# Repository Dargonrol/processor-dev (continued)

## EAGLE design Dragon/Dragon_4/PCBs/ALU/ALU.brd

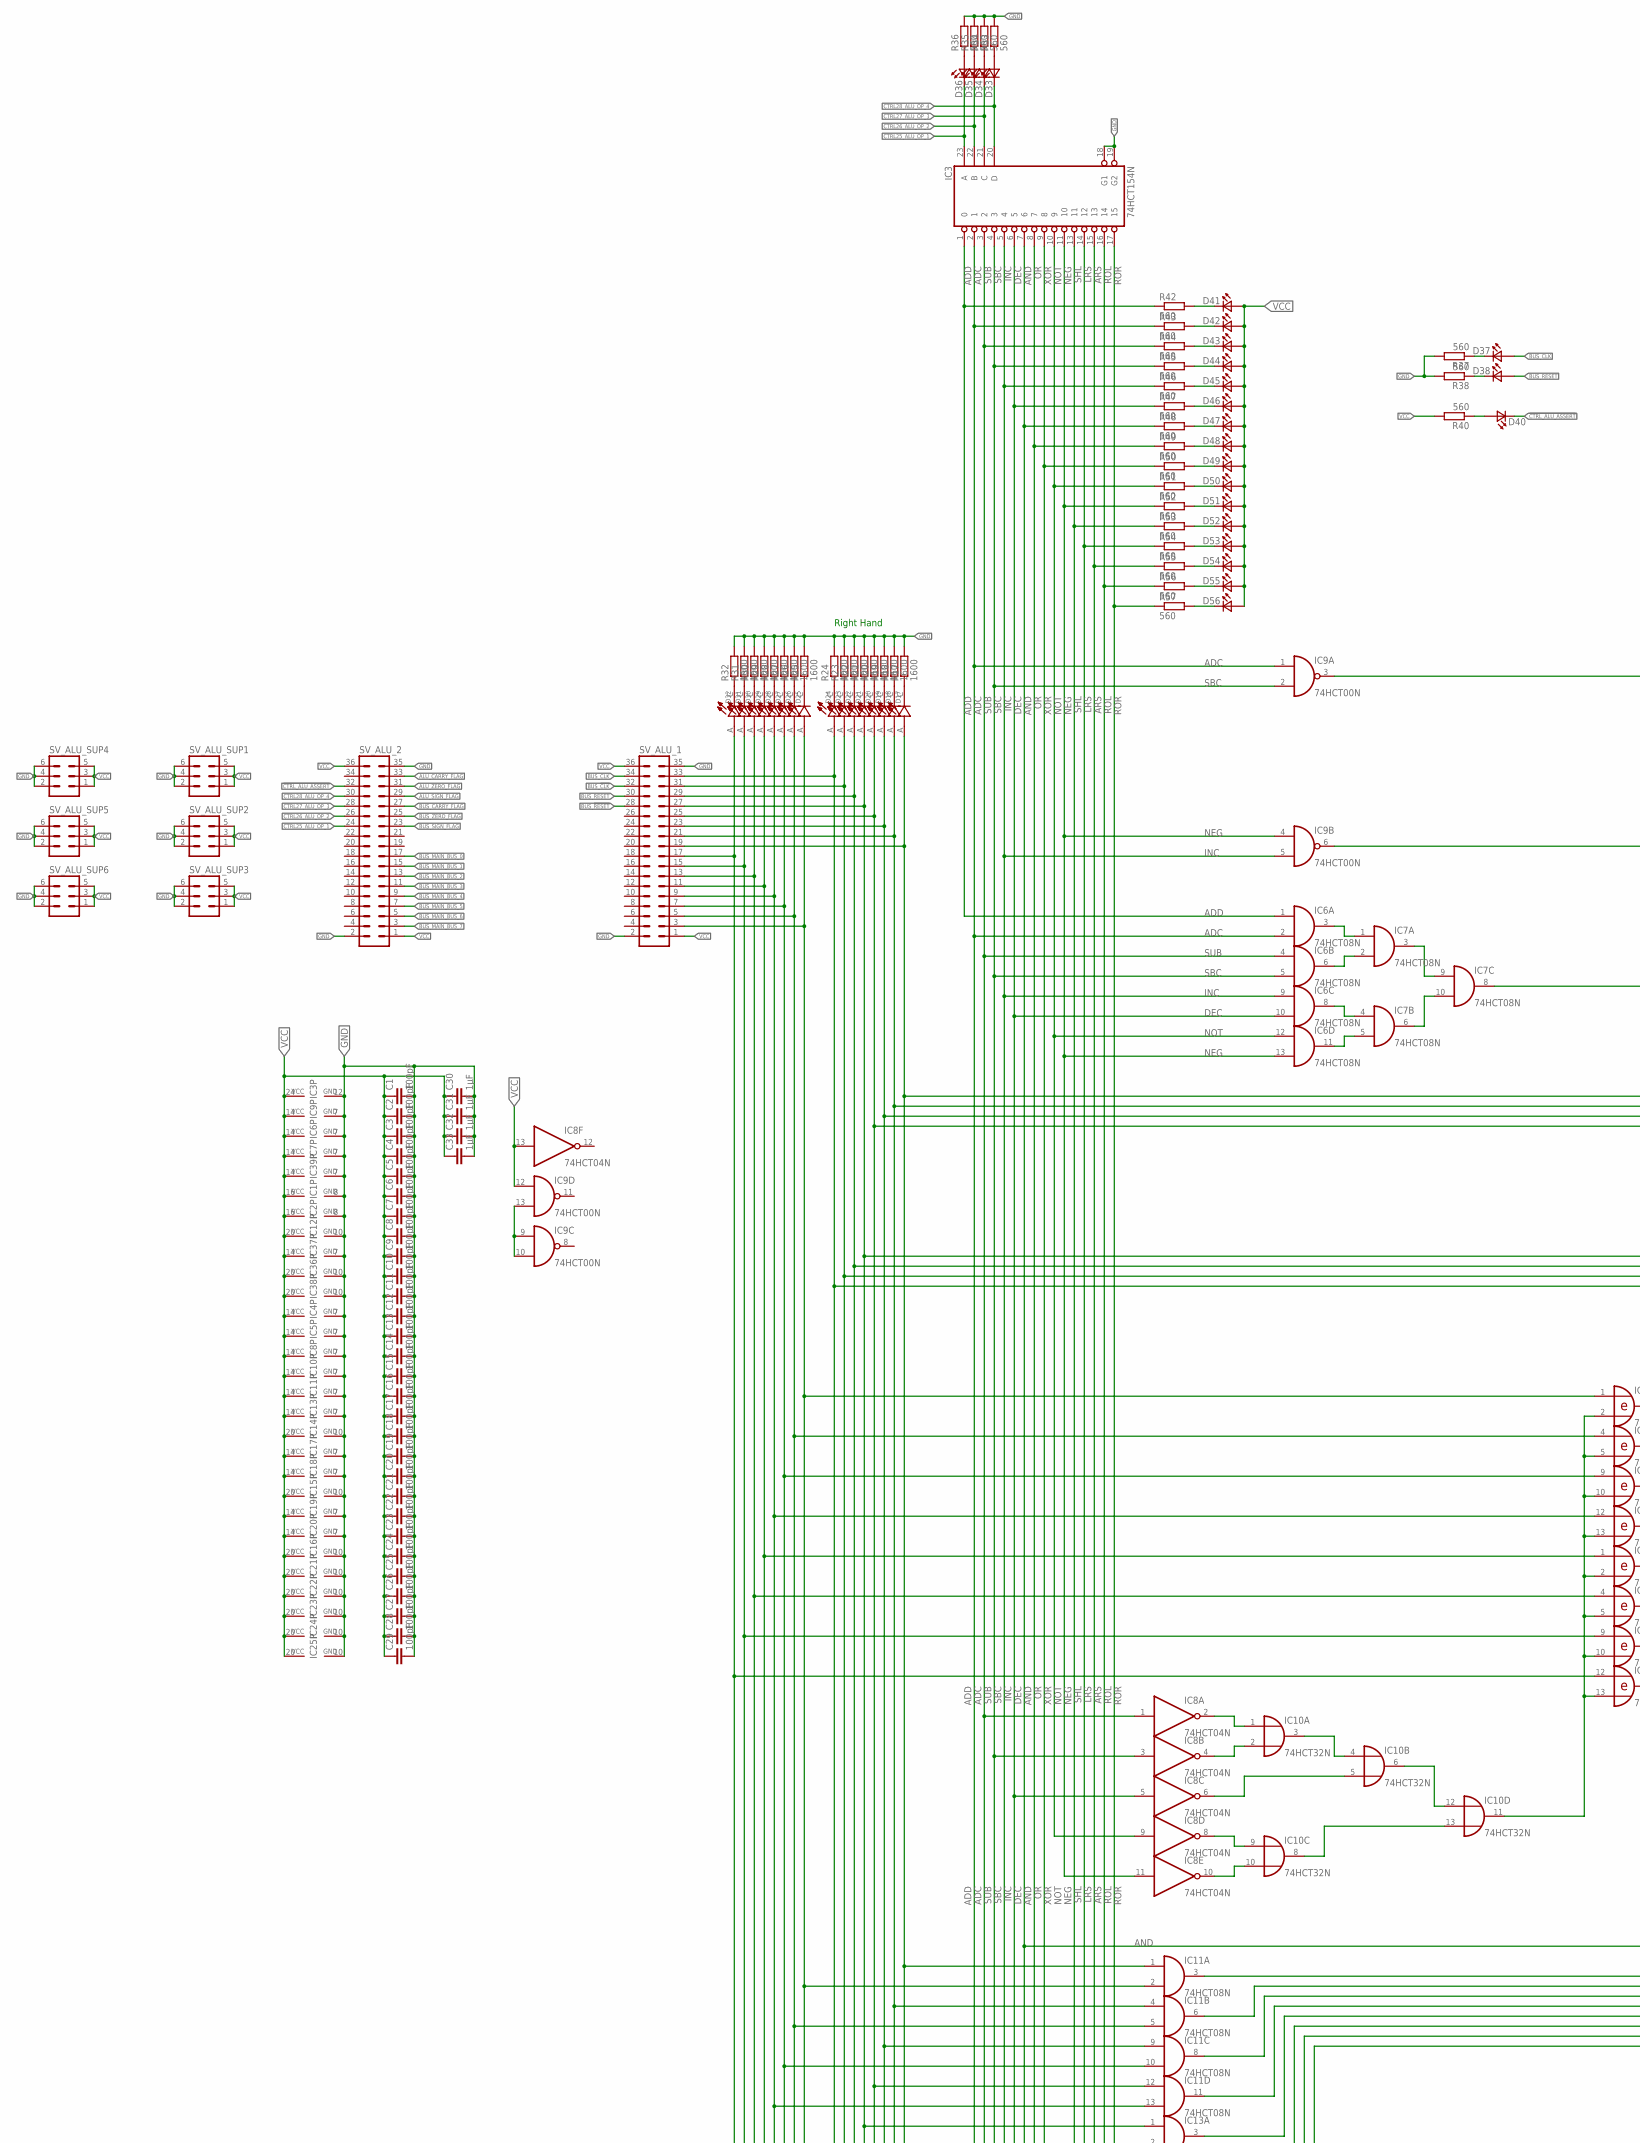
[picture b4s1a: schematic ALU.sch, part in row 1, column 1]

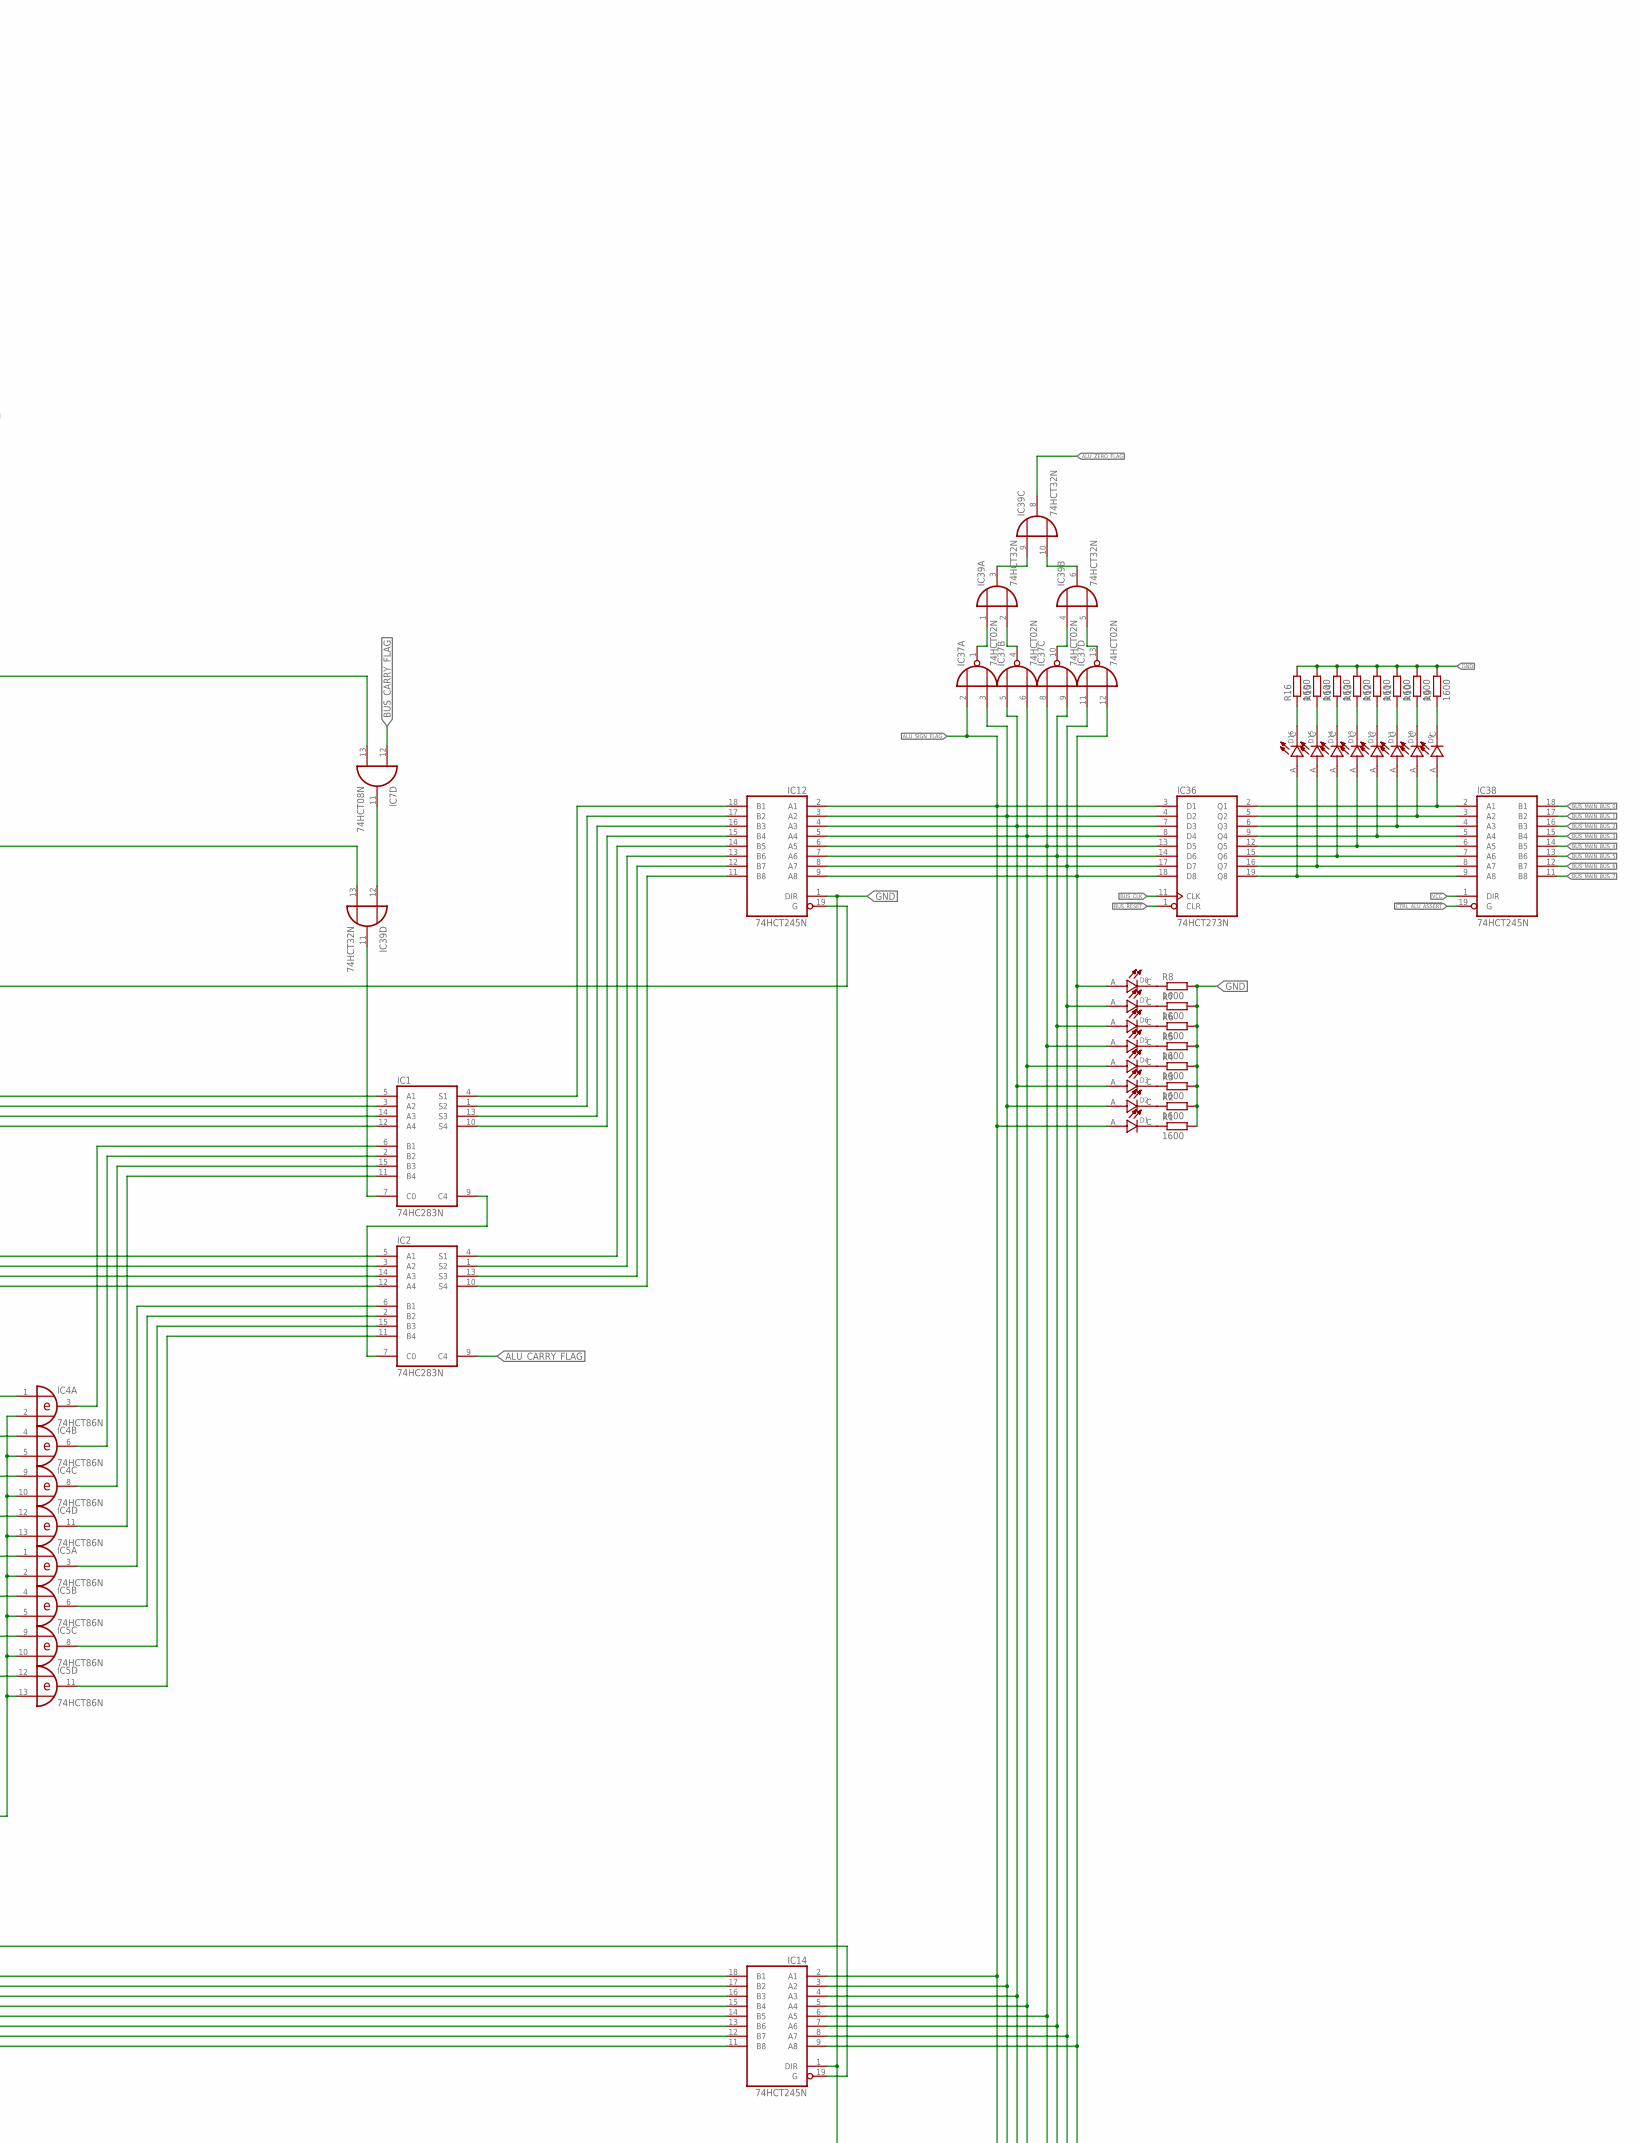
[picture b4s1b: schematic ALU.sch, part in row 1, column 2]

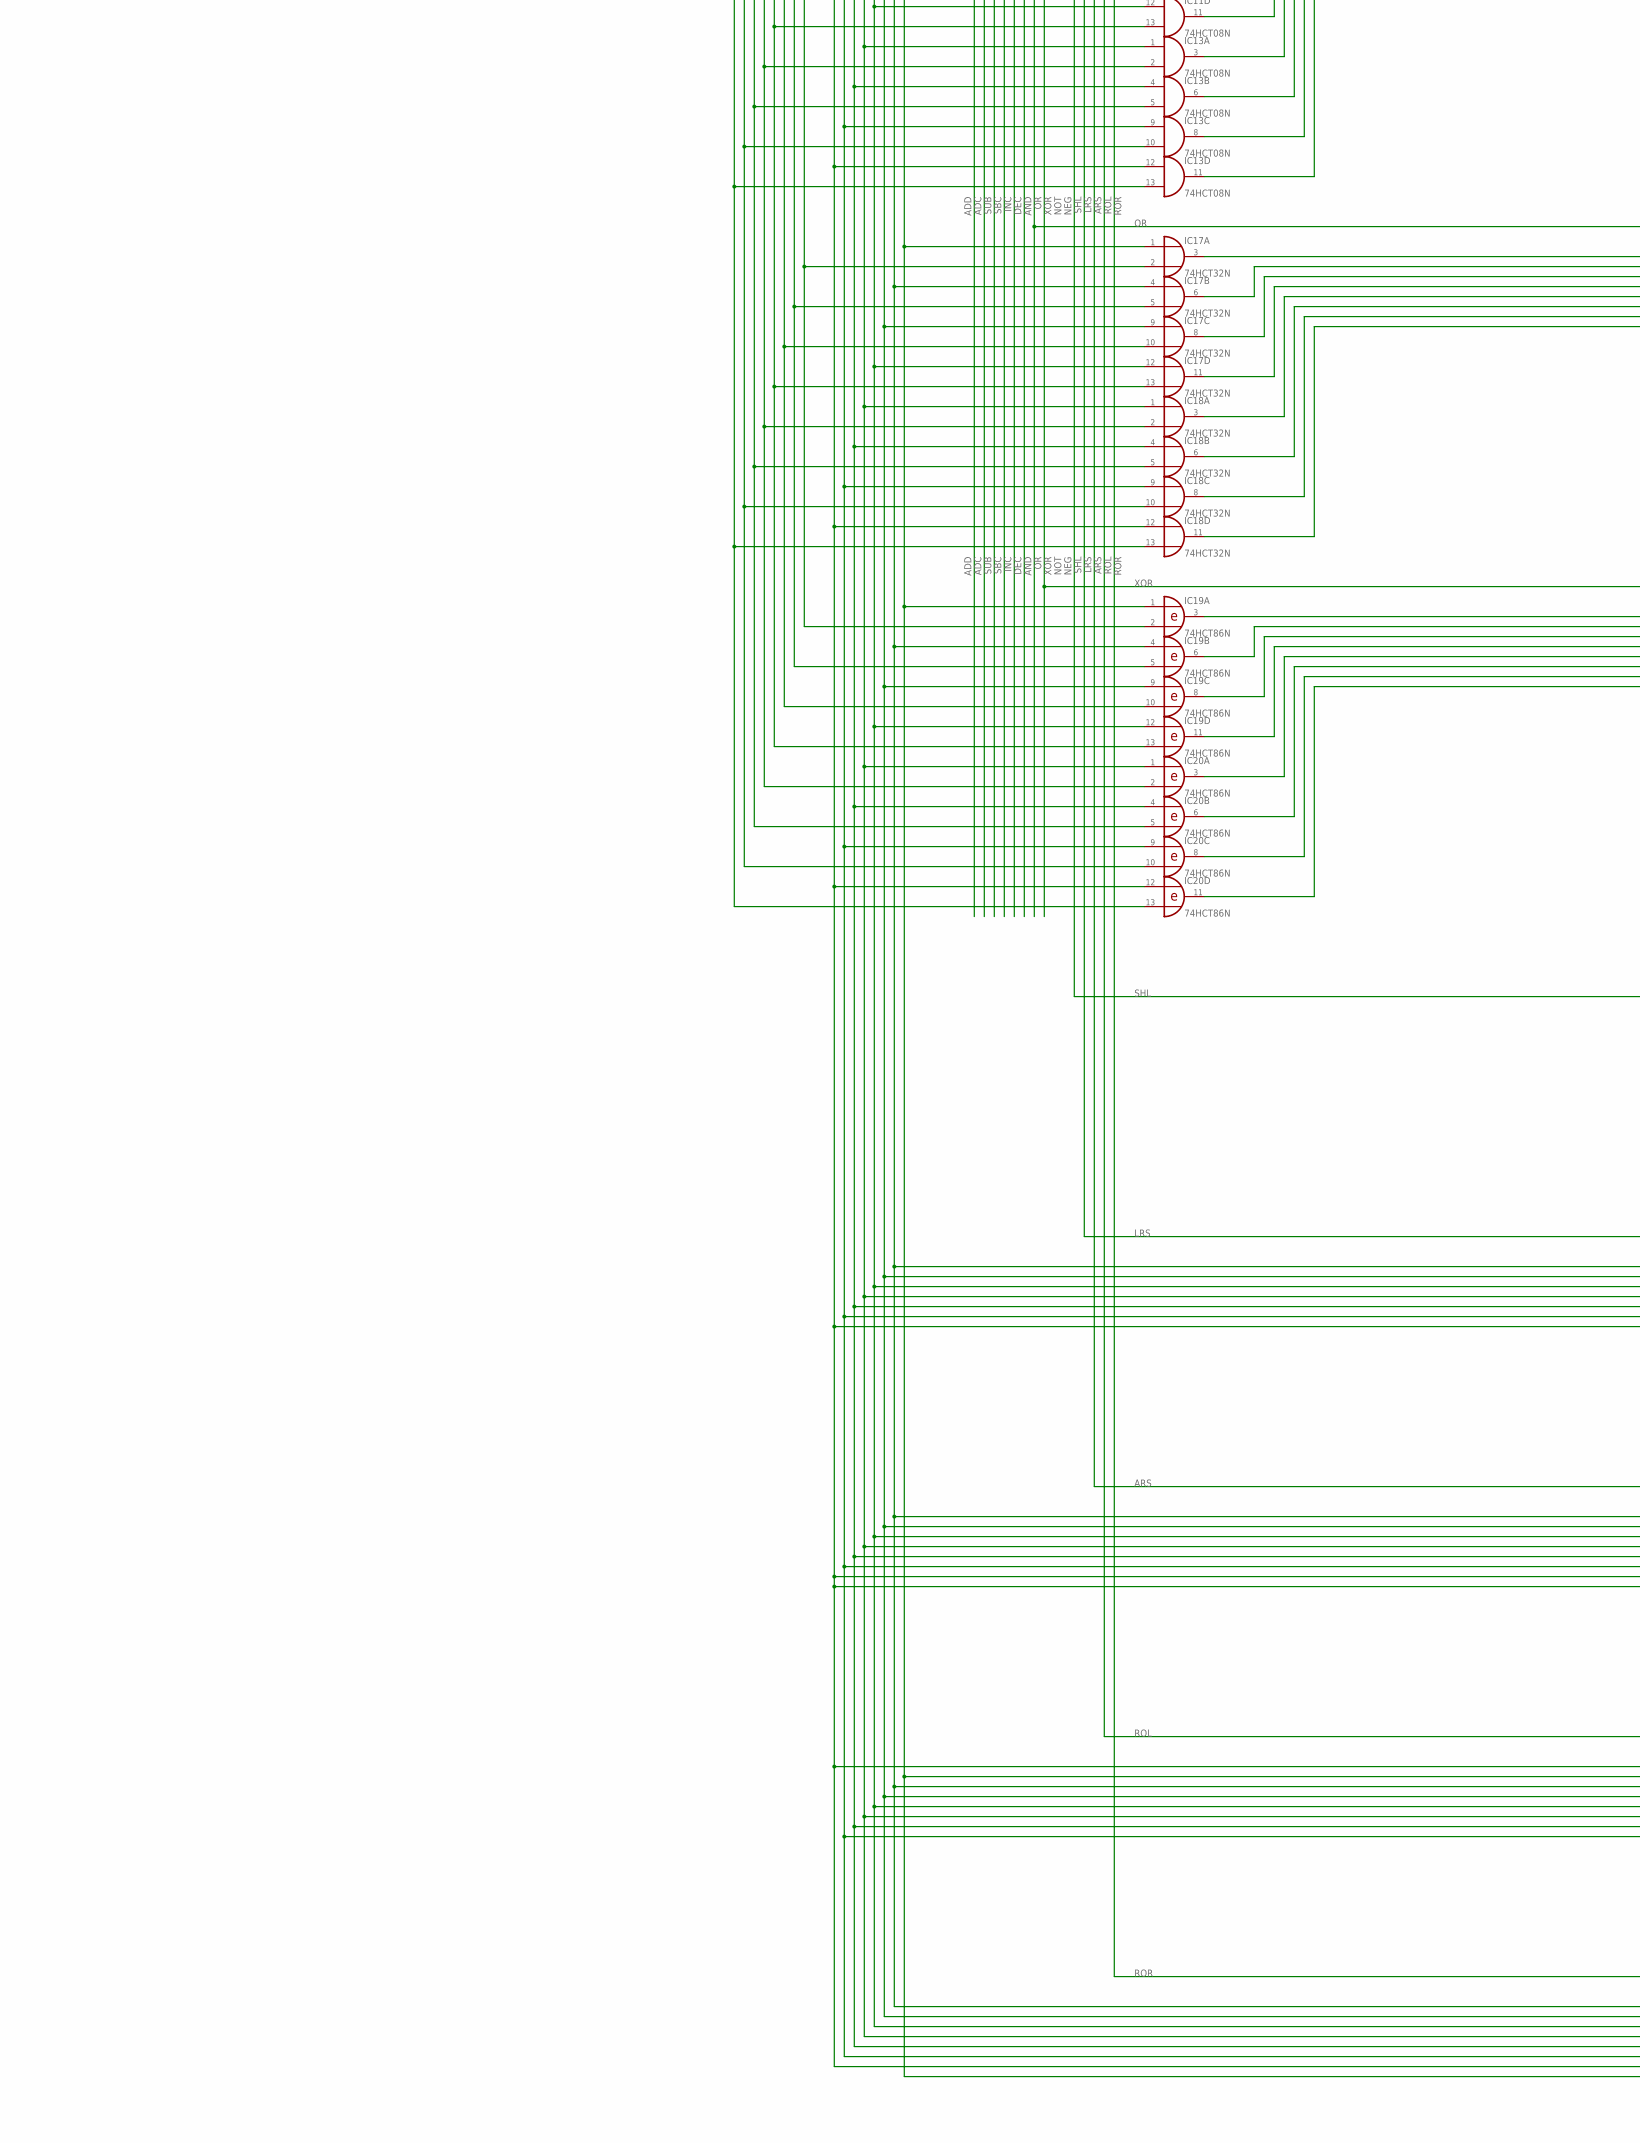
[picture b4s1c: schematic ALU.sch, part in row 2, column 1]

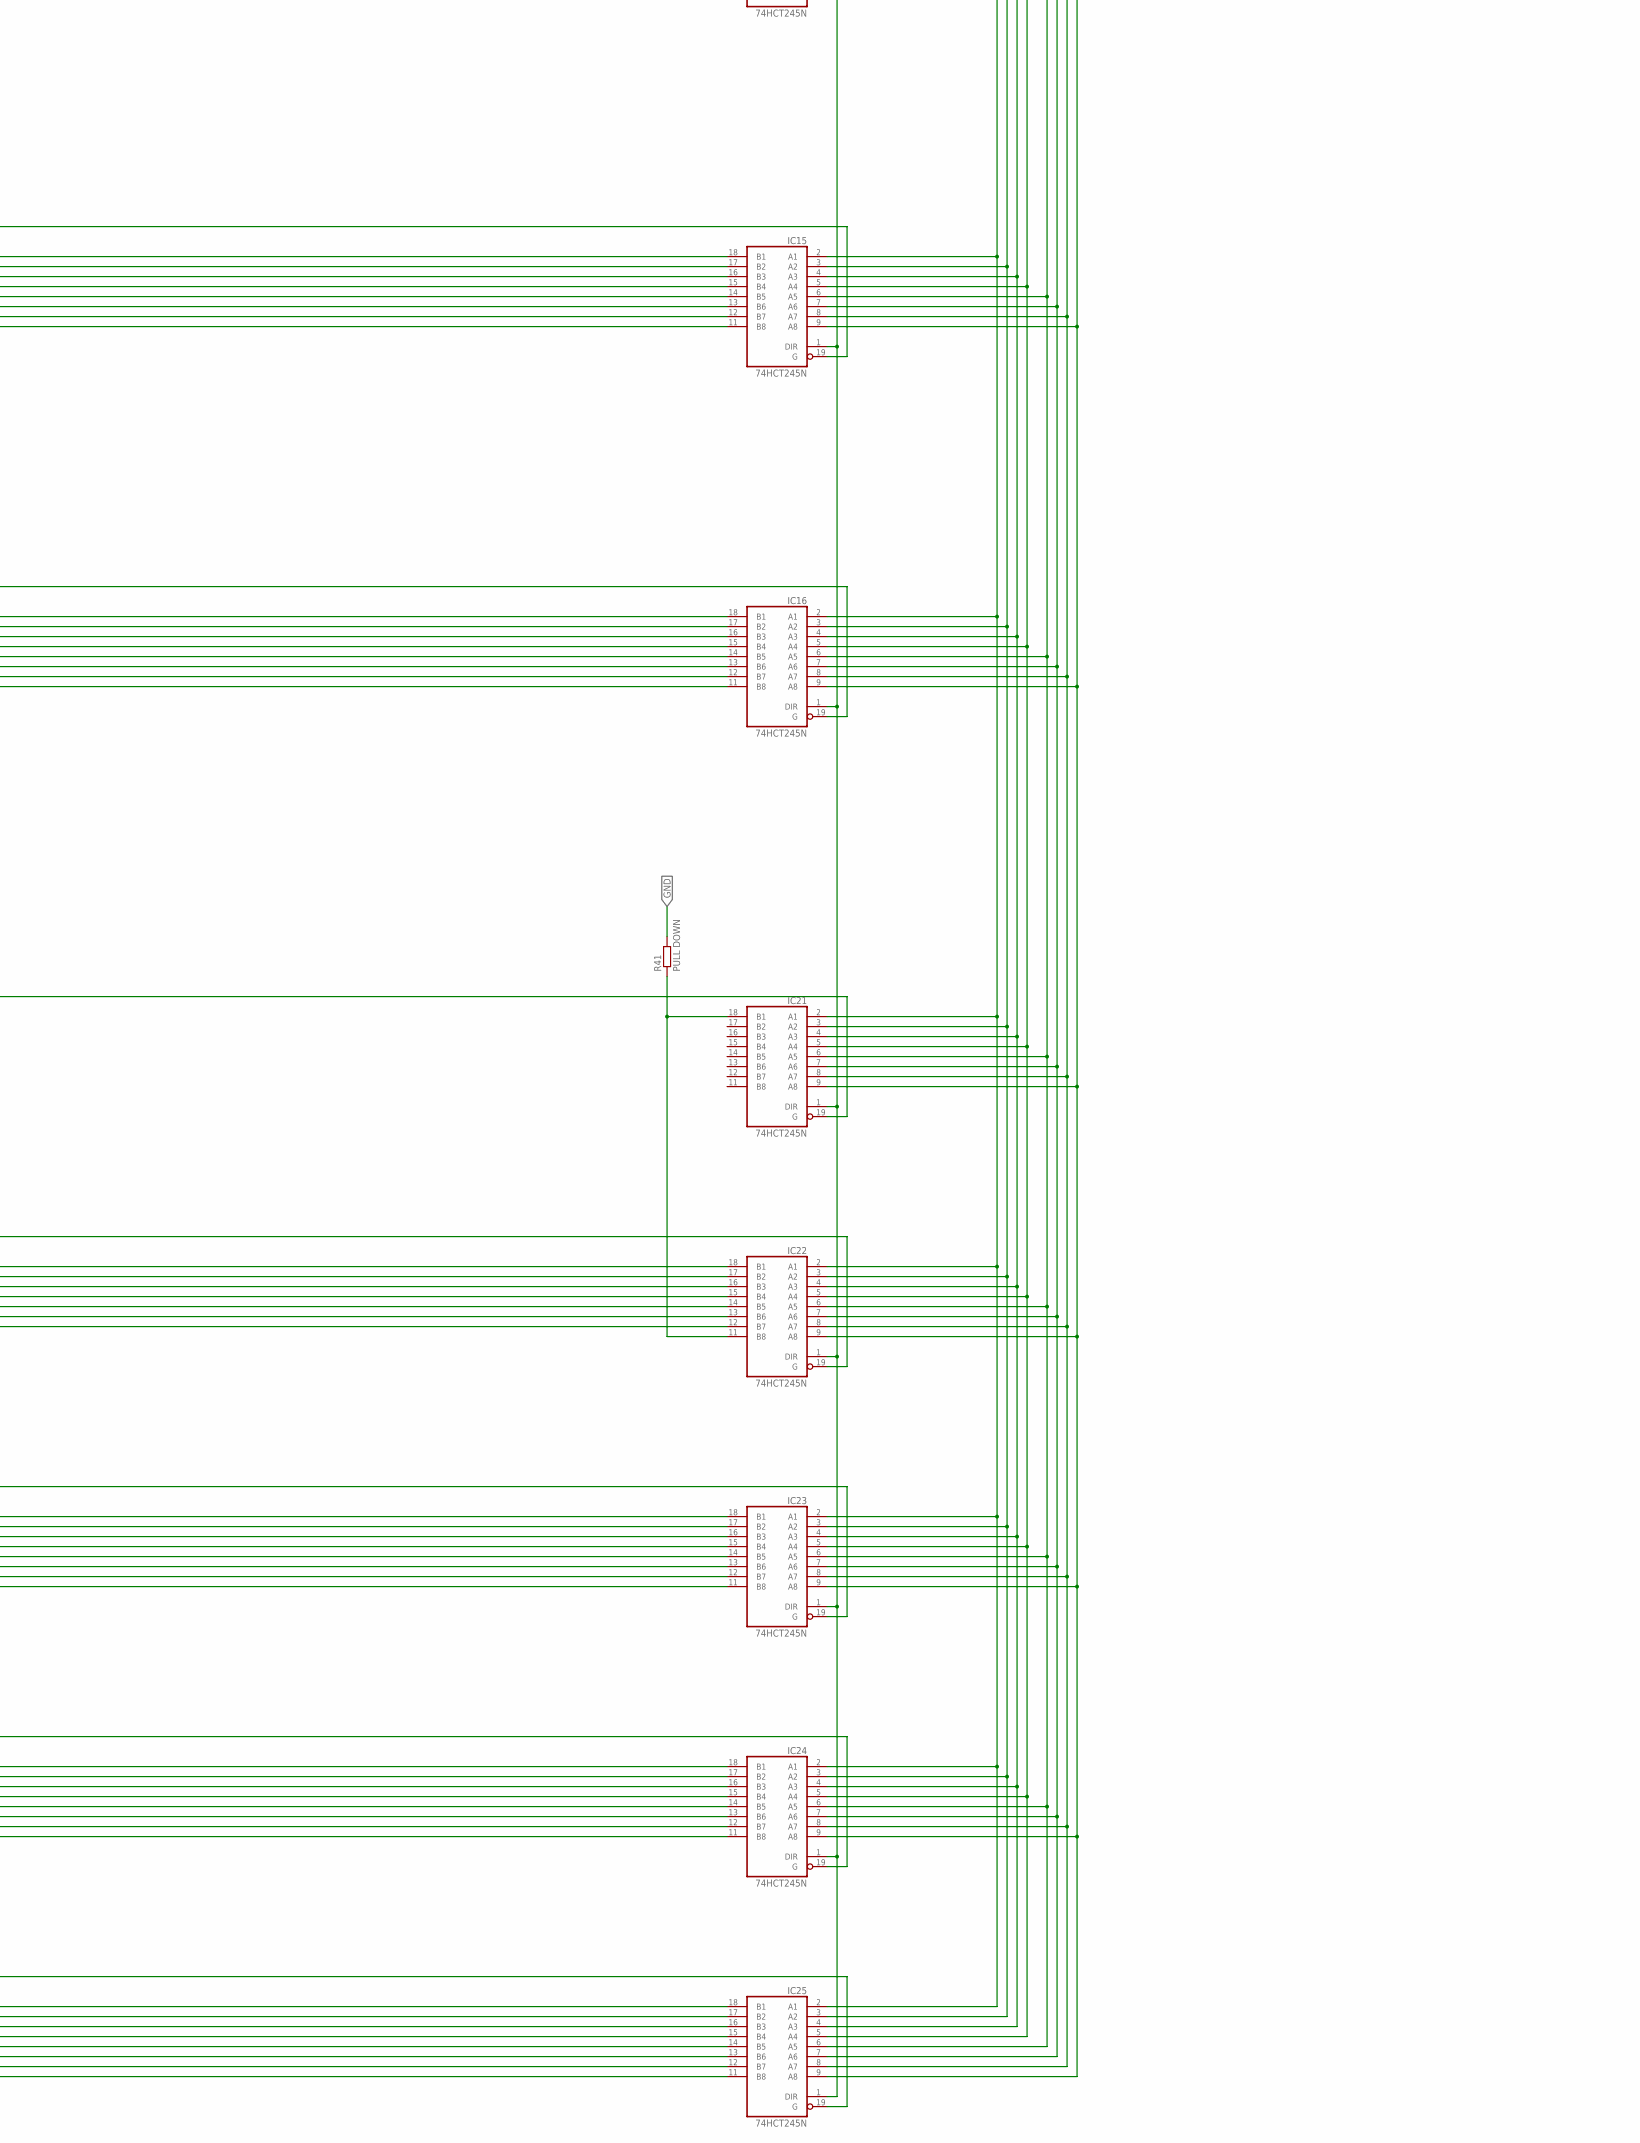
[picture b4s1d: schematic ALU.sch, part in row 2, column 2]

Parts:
C1, C2, C3, C4, C5, C6, C7, C8, C9, C10, C11, C12, C13, C14, C15, C16, C17, C18, C19, C20, C21, C22, C23, C24, C25, C26, C27, C28, C29: 100pF; C0805
C30, C31, C32, C33: 1µF; C0805
D1, D2, D3, D4, D5, D6, D7, D8, D9, D10, D11, D12, D13, D14, D15, D16, D17, D18, D19, D20, D21, D22, D23, D24, D25, D26, D27, D28, D29, D30, D31, D32: LTST-C193KRKT-5A; LEDC1608X45N
D33, D34, D35, D36, D37, D38, D40, D41, D42, D43, D44, D45, D46, D47, D48, D49, D50, D51, D52, D53, D54, D55, D56: LTST-C193TBKT-5A; 0603
IC1, IC2: 74HC283N; DIL16
IC3: 74HCT154N; DIL24-6
IC4, IC5, IC19, IC20: 74HCT86N; DIL14
IC6, IC7, IC11, IC13: 74HCT08N; DIL14
IC8: 74HCT04N; DIL14
IC9: 74HCT00N; DIL14
IC10, IC17, IC18, IC39: 74HCT32N; DIL14
IC12, IC14, IC15, IC16, IC21, IC22, IC23, IC24, IC25, IC38: 74HCT245N; DIL20
IC36: 74HCT273N; DIL20
IC37: 74HCT02N; DIL14
R1, R2, R3, R4, R5, R6, R7, R8, R9, R10, R11, R12, R13, R14, R15, R16, R17, R18, R19, R20, R21, R22, R23, R24, R25, R26, R27, R28, R29, R30, R31, R32: 1600; R0805
R33, R34, R35, R36, R37, R38, R40, R42, R43, R44, R45, R46, R47, R48, R49, R50, R51, R52, R53, R54, R55, R56, R57: 560; R0805
R41: PULL DOWN; R0805
SV_ALU_1, SV_ALU_2: MA18-2
SV_ALU_SUP1, SV_ALU_SUP2, SV_ALU_SUP3, SV_ALU_SUP4, SV_ALU_SUP5, SV_ALU_SUP6: MA03-2

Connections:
!CTRL_ALU_ASSERT: D40.1 (K2), IC38.19 (G), SV_ALU_2.32
ADC: IC3.2 (1), IC6.2 (I1), IC9.1 (I0), R43.1
ADD: IC3.1 (0), IC6.1 (I0), R42.1
ALU_CARRY_FLAG: IC2.9 (C4), SV_ALU_2.33
ALU_SIGN_FLAG: D1.A, IC12.2 (A1), IC14.2 (A1), IC15.2 (A1), IC16.2 (A1), IC21.2 (A1), IC22.2 (A1), IC23.2 (A1), IC24.2 (A1), IC25.2 (A1), IC36.3 (D1), IC37.2 (I0), SV_ALU_2.29
ALU_ZERO_FLAG: IC39.8 (O), SV_ALU_2.31
AND: IC3.7 (6), IC14.19 (G), R48.1
ARS: IC3.15 (13), IC23.19 (G), R55.1
BUS_!CLK: SV_ALU_1.32
BUS_!RESET: IC36.1 (CLR), SV_ALU_1.28
BUS_CARRY_FLAG: IC7.12 (I0), SV_ALU_2.27
BUS_CLK: D37.2 (A2), IC36.11 (CLK), SV_ALU_1.34
BUS_MAIN_BUS_0: IC38.18 (B1), SV_ALU_2.17
BUS_MAIN_BUS_1: IC38.17 (B2), SV_ALU_2.15
BUS_MAIN_BUS_2: IC38.16 (B3), SV_ALU_2.13
BUS_MAIN_BUS_3: IC38.15 (B4), SV_ALU_2.11
BUS_MAIN_BUS_4: IC38.14 (B5), SV_ALU_2.9
BUS_MAIN_BUS_5: IC38.13 (B6), SV_ALU_2.7
BUS_MAIN_BUS_6: IC38.12 (B7), SV_ALU_2.5
BUS_MAIN_BUS_7: IC38.11 (B8), SV_ALU_2.3
BUS_RESET: D38.2 (A2), SV_ALU_1.30
BUS_SIGN_FLAG: SV_ALU_2.23
BUS_ZERO_FLAG: SV_ALU_2.25
CTRL25_ALU_OP_1: D36.1 (K2), IC3.23 (A), SV_ALU_2.24
CTRL26_ALU_OP_2: D35.1 (K2), IC3.22 (B), SV_ALU_2.26
CTRL27_ALU_OP_3: D34.1 (K2), IC3.21 (C), SV_ALU_2.28
CTRL28_ALU_OP_4: D33.1 (K2), IC3.20 (D), SV_ALU_2.30
DEC: IC3.6 (5), IC6.10 (I1), IC8.5 (I), R47.1
GND: C1.2, C2.2, C3.2, C4.2, C5.2, C6.2, C7.2, C8.2, C9.2, C10.2, C11.2, C12.2, C13.2, C14.2, C15.2, C16.2, C17.2, C18.2, C19.2, C20.2, C21.2, C22.2, C23.2, C24.2, C25.2, C26.2, C27.2, C28.2, C29.2, C30.2, C31.2, C32.2, C33.2, IC1.8 (GND), IC2.8 (GND), IC3.12 (GND), IC3.18 (G1), IC3.19 (G2), IC4.7 (GND), IC5.7 (GND), IC6.7 (GND), IC7.7 (GND), IC8.7 (GND), IC9.7 (GND), IC10.7 (GND), IC11.7 (GND), IC12.1 (DIR), IC12.10 (GND), IC13.7 (GND), IC14.1 (DIR), IC14.10 (GND), IC15.1 (DIR), IC15.10 (GND), IC16.1 (DIR), IC16.10 (GND), IC17.7 (GND), IC18.7 (GND), IC19.7 (GND), IC20.7 (GND), IC21.1 (DIR), IC21.10 (GND), IC22.1 (DIR), IC22.10 (GND), IC23.1 (DIR), IC23.10 (GND), IC24.1 (DIR), IC24.10 (GND), IC25.1 (DIR), IC25.10 (GND), IC36.10 (GND), IC37.7 (GND), IC38.10 (GND), IC39.7 (GND), R1.2, R2.2, R3.2, R4.2, R5.2, R6.2, R7.2, R8.2, R9.2, R10.2, R11.2, R12.2, R13.2, R14.2, R15.2, R16.2, R17.2, R18.2, R19.2, R20.2, R21.2, R22.2, R23.2, R24.2, R25.2, R26.2, R27.2, R28.2, R29.2, R30.2, R31.2, R32.2, R33.2, R34.2, R35.2, R36.2, R37.2, R38.2, R41.2, SV_ALU_1.2, SV_ALU_1.35, SV_ALU_2.2, SV_ALU_2.35, SV_ALU_SUP1.2, SV_ALU_SUP1.4, SV_ALU_SUP1.6, SV_ALU_SUP2.2, SV_ALU_SUP2.4, SV_ALU_SUP2.6, SV_ALU_SUP3.2, SV_ALU_SUP3.4, SV_ALU_SUP3.6, SV_ALU_SUP4.2, SV_ALU_SUP4.4, SV_ALU_SUP4.6, SV_ALU_SUP5.2, SV_ALU_SUP5.4, SV_ALU_SUP5.6, SV_ALU_SUP6.2, SV_ALU_SUP6.4, SV_ALU_SUP6.6
INC: IC3.5 (4), IC6.9 (I0), IC9.5 (I1), R46.1
LRS: IC3.14 (12), IC22.19 (G), R54.1
unnamed: IC4.2 (I1), IC4.5 (I1), IC4.10 (I1), IC4.13 (I1), IC5.2 (I1), IC5.5 (I1), IC5.10 (I1), IC5.13 (I1), IC10.11 (O)
unnamed: IC1.6 (B1), IC4.3 (O)
unnamed: D33.2 (A2), R33.1
unnamed: IC1.2 (B2), IC4.6 (O)
unnamed: D27.A, IC4.9 (I0), IC11.10 (I1), IC17.10 (I1), IC19.10 (I1), SV_ALU_1.7
unnamed: IC1.15 (B3), IC4.8 (O)
unnamed: IC1.11 (B4), IC4.11 (O)
unnamed: IC2.6 (B1), IC5.3 (O)
unnamed: IC2.2 (B2), IC5.6 (O)
unnamed: IC2.15 (B3), IC5.8 (O)
unnamed: IC2.11 (B4), IC5.11 (O)
unnamed: IC1.9 (C4), IC2.7 (C0)
unnamed: IC1.7 (C0), IC39.11 (O)
unnamed: IC1.4 (S1), IC12.18 (B1)
unnamed: IC1.1 (S2), IC12.17 (B2)
unnamed: D16.C, R16.1
unnamed: IC1.13 (S3), IC12.16 (B3)
unnamed: IC1.10 (S4), IC12.15 (B4)
unnamed: IC2.4 (S1), IC12.14 (B5)
unnamed: IC37.1 (O), IC39.1 (I0)
unnamed: IC37.4 (O), IC39.2 (I1)
unnamed: IC37.10 (O), IC39.4 (I0)
unnamed: IC37.13 (O), IC39.5 (I1)
unnamed: D15.C, R15.1
unnamed: IC39.6 (O), IC39.10 (I1)
unnamed: IC39.3 (O), IC39.9 (I0)
unnamed: D34.2 (A2), R34.1
unnamed: D35.2 (A2), R35.1
unnamed: D36.2 (A2), R36.1
unnamed: D40.2 (A2), R40.1
unnamed: IC2.1 (S2), IC12.13 (B6)
unnamed: IC2.13 (S3), IC12.12 (B7)
unnamed: IC2.10 (S4), IC12.11 (B8)
unnamed: IC6.3 (O), IC7.1 (I0)
unnamed: IC6.6 (O), IC7.2 (I1)
unnamed: IC6.8 (O), IC7.4 (I0)
unnamed: IC6.11 (O), IC7.5 (I1)
unnamed: IC7.3 (O), IC7.9 (I0)
unnamed: IC7.6 (O), IC7.10 (I1)
unnamed: IC7.8 (O), IC12.19 (G)
unnamed: IC7.11 (O), IC39.12 (I0)
unnamed: IC9.6 (O), IC39.13 (I1)
unnamed: IC7.13 (I1), IC9.3 (O)
unnamed: IC8.2 (O), IC10.1 (I0)
unnamed: IC8.4 (O), IC10.2 (I1)
unnamed: IC10.3 (O), IC10.4 (I0)
unnamed: IC8.6 (O), IC10.5 (I1)
unnamed: IC8.8 (O), IC10.9 (I0)
unnamed: IC8.10 (O), IC10.10 (I1)
unnamed: D1.C, R1.1
unnamed: IC10.8 (O), IC10.13 (I1)
unnamed: IC10.6 (O), IC10.12 (I0)
unnamed: D41.1 (K2), R42.2
unnamed: IC11.6 (O), IC14.17 (B2)
unnamed: IC11.8 (O), IC14.16 (B3)
unnamed: IC11.11 (O), IC14.15 (B4)
unnamed: IC13.3 (O), IC14.14 (B5)
unnamed: IC13.6 (O), IC14.13 (B6)
unnamed: IC13.8 (O), IC14.12 (B7)
unnamed: IC13.11 (O), IC14.11 (B8)
unnamed: IC16.18 (B1), IC19.3 (O)
unnamed: D14.C, R14.1
unnamed: D21.A, IC2.5 (A1), IC13.1 (I0), IC18.1 (I0), IC20.1 (I0), IC22.15 (B4), IC23.15 (B4), IC24.13 (B6), IC25.15 (B4), SV_ALU_1.27
unnamed: D22.A, IC2.3 (A2), IC13.4 (I0), IC18.4 (I0), IC20.4 (I0), IC22.14 (B5), IC23.14 (B5), IC24.12 (B7), IC25.14 (B5), SV_ALU_1.29
unnamed: D23.A, IC2.14 (A3), IC13.9 (I0), IC18.9 (I0), IC20.9 (I0), IC22.13 (B6), IC23.13 (B6), IC24.11 (B8), IC25.13 (B6), SV_ALU_1.31
unnamed: D24.A, IC2.12 (A4), IC13.12 (I0), IC18.12 (I0), IC20.12 (I0), IC22.12 (B7), IC23.11 (B8), IC23.12 (B7), IC24.18 (B1), IC25.12 (B7), SV_ALU_1.33
unnamed: D2.C, R2.1
unnamed: D32.A, IC5.12 (I0), IC13.13 (I1), IC18.13 (I1), IC20.13 (I1), SV_ALU_1.17
unnamed: IC15.17 (B2), IC17.6 (O)
unnamed: D13.C, R13.1
unnamed: D12.C, R12.1
unnamed: IC15.16 (B3), IC17.8 (O)
unnamed: IC15.15 (B4), IC17.11 (O)
unnamed: IC15.14 (B5), IC18.3 (O)
unnamed: IC15.13 (B6), IC18.6 (O)
unnamed: D38.1 (K2), R38.1
unnamed: D37.1 (K2), R37.1
unnamed: D17.A, IC1.5 (A1), IC11.1 (I0), IC17.1 (I0), IC19.1 (I0), IC24.17 (B2), IC25.11 (B8), SV_ALU_1.19
unnamed: D18.A, IC1.3 (A2), IC11.4 (I0), IC17.4 (I0), IC19.4 (I0), IC22.18 (B1), IC23.18 (B1), IC24.16 (B3), IC25.18 (B1), SV_ALU_1.21
unnamed: D19.A, IC1.14 (A3), IC11.9 (I0), IC17.9 (I0), IC19.9 (I0), IC22.17 (B2), IC23.17 (B2), IC24.15 (B4), IC25.17 (B2), SV_ALU_1.23
unnamed: D20.A, IC1.12 (A4), IC11.12 (I0), IC17.12 (I0), IC19.12 (I0), IC22.16 (B3), IC23.16 (B3), IC24.14 (B5), IC25.16 (B3), SV_ALU_1.25
unnamed: IC15.12 (B7), IC18.8 (O)
unnamed: IC15.11 (B8), IC18.11 (O)
unnamed: IC15.18 (B1), IC17.3 (O)
unnamed: IC16.17 (B2), IC19.6 (O)
unnamed: IC16.16 (B3), IC19.8 (O)
unnamed: IC16.15 (B4), IC19.11 (O)
unnamed: IC16.14 (B5), IC20.3 (O)
unnamed: IC16.13 (B6), IC20.6 (O)
unnamed: IC16.12 (B7), IC20.8 (O)
unnamed: IC16.11 (B8), IC20.11 (O)
unnamed: IC21.18 (B1), IC22.11 (B8), R41.1
unnamed: IC9.9 (I0), IC9.10 (I1), IC9.13 (I1)
unnamed: IC11.3 (O), IC14.18 (B1)
unnamed: D42.1 (K2), R43.2
unnamed: D43.1 (K2), R44.2
unnamed: D44.1 (K2), R45.2
unnamed: D45.1 (K2), R46.2
unnamed: D46.1 (K2), R47.2
unnamed: D47.1 (K2), R48.2
unnamed: D48.1 (K2), R49.2
unnamed: D49.1 (K2), R50.2
unnamed: D50.1 (K2), R51.2
unnamed: D51.1 (K2), R52.2
unnamed: D52.1 (K2), R53.2
unnamed: D53.1 (K2), R54.2
unnamed: D54.1 (K2), R55.2
unnamed: D55.1 (K2), R56.2
unnamed: D56.1 (K2), R57.2
unnamed: D25.A, IC4.1 (I0), IC11.2 (I1), IC17.2 (I1), IC19.2 (I1), SV_ALU_1.3
unnamed: D26.A, IC4.4 (I0), IC11.5 (I1), IC17.5 (I1), IC19.5 (I1), SV_ALU_1.5
unnamed: D28.A, IC4.12 (I0), IC11.13 (I1), IC17.13 (I1), IC19.13 (I1), SV_ALU_1.9
unnamed: D29.A, IC5.1 (I0), IC13.2 (I1), IC18.2 (I1), IC20.2 (I1), SV_ALU_1.11
unnamed: D30.A, IC5.4 (I0), IC13.5 (I1), IC18.5 (I1), IC20.5 (I1), SV_ALU_1.13
unnamed: D31.A, IC5.9 (I0), IC13.10 (I1), IC18.10 (I1), IC20.10 (I1), SV_ALU_1.15
unnamed: D2.A, IC12.3 (A2), IC14.3 (A2), IC15.3 (A2), IC16.3 (A2), IC21.3 (A2), IC22.3 (A2), IC23.3 (A2), IC24.3 (A2), IC25.3 (A2), IC36.4 (D2), IC37.3 (I1)
unnamed: D3.A, IC12.4 (A3), IC14.4 (A3), IC15.4 (A3), IC16.4 (A3), IC21.4 (A3), IC22.4 (A3), IC23.4 (A3), IC24.4 (A3), IC25.4 (A3), IC36.7 (D3), IC37.5 (I0)
unnamed: D4.A, IC12.5 (A4), IC14.5 (A4), IC15.5 (A4), IC16.5 (A4), IC21.5 (A4), IC22.5 (A4), IC23.5 (A4), IC24.5 (A4), IC25.5 (A4), IC36.8 (D4), IC37.6 (I1)
unnamed: D11.C, R11.1
unnamed: D10.C, R10.1
unnamed: D9.C, R9.1
unnamed: D3.C, R3.1
unnamed: D4.C, R4.1
unnamed: D5.C, R5.1
unnamed: D6.C, R6.1
unnamed: D7.C, R7.1
unnamed: D8.C, R8.1
unnamed: D17.C, R17.1
unnamed: D18.C, R18.1
unnamed: D19.C, R19.1
unnamed: D20.C, R20.1
unnamed: D21.C, R21.1
unnamed: D22.C, R22.1
unnamed: D23.C, R23.1
unnamed: D24.C, R24.1
unnamed: D25.C, R25.1
unnamed: D26.C, R26.1
unnamed: D27.C, R27.1
unnamed: D28.C, R28.1
unnamed: D29.C, R29.1
unnamed: D30.C, R30.1
unnamed: D16.A, IC36.19 (Q8), IC38.9 (A8)
unnamed: D15.A, IC36.16 (Q7), IC38.8 (A7)
unnamed: D14.A, IC36.15 (Q6), IC38.7 (A6)
unnamed: D13.A, IC36.12 (Q5), IC38.6 (A5)
unnamed: D12.A, IC36.9 (Q4), IC38.5 (A4)
unnamed: D11.A, IC36.6 (Q3), IC38.4 (A3)
unnamed: D10.A, IC36.5 (Q2), IC38.3 (A2)
unnamed: D9.A, IC36.2 (Q1), IC38.2 (A1)
unnamed: D31.C, R31.1
unnamed: D32.C, R32.1
unnamed: D5.A, IC12.6 (A5), IC14.6 (A5), IC15.6 (A5), IC16.6 (A5), IC21.6 (A5), IC22.6 (A5), IC23.6 (A5), IC24.6 (A5), IC25.6 (A5), IC36.13 (D5), IC37.8 (I0)
unnamed: D7.A, IC12.8 (A7), IC14.8 (A7), IC15.8 (A7), IC16.8 (A7), IC21.8 (A7), IC22.8 (A7), IC23.8 (A7), IC24.8 (A7), IC25.8 (A7), IC36.17 (D7), IC37.11 (I0)
unnamed: D8.A, IC12.9 (A8), IC14.9 (A8), IC15.9 (A8), IC16.9 (A8), IC21.9 (A8), IC22.9 (A8), IC23.9 (A8), IC24.9 (A8), IC25.9 (A8), IC36.18 (D8), IC37.12 (I1)
unnamed: D6.A, IC12.7 (A6), IC14.7 (A6), IC15.7 (A6), IC16.7 (A6), IC21.7 (A6), IC22.7 (A6), IC23.7 (A6), IC24.7 (A6), IC25.7 (A6), IC36.14 (D6), IC37.9 (I1)
NEG: IC3.11 (10), IC6.13 (I1), IC8.11 (I), IC9.4 (I0), R52.1
NOT: IC3.10 (9), IC6.12 (I0), IC8.9 (I), R51.1
OR: IC3.8 (7), IC15.19 (G), R49.1
ROL: IC3.16 (14), IC24.19 (G), R56.1
ROR: IC3.17 (15), IC25.19 (G), R57.1
SBC: IC3.4 (3), IC6.5 (I1), IC8.3 (I), IC9.2 (I1), R45.1
SHL: IC3.13 (11), IC21.19 (G), R53.1
SUB: IC3.3 (2), IC6.4 (I0), IC8.1 (I), R44.1
VCC: C1.1, C2.1, C3.1, C4.1, C5.1, C6.1, C7.1, C8.1, C9.1, C10.1, C11.1, C12.1, C13.1, C14.1, C15.1, C16.1, C17.1, C18.1, C19.1, C20.1, C21.1, C22.1, C23.1, C24.1, C25.1, C26.1, C27.1, C28.1, C29.1, C30.1, C31.1, C32.1, C33.1, D41.2 (A2), D42.2 (A2), D43.2 (A2), D44.2 (A2), D45.2 (A2), D46.2 (A2), D47.2 (A2), D48.2 (A2), D49.2 (A2), D50.2 (A2), D51.2 (A2), D52.2 (A2), D53.2 (A2), D54.2 (A2), D55.2 (A2), D56.2 (A2), IC1.16 (VCC), IC2.16 (VCC), IC3.24 (VCC), IC4.14 (VCC), IC5.14 (VCC), IC6.14 (VCC), IC7.14 (VCC), IC8.13 (I), IC8.14 (VCC), IC9.12 (I0), IC9.14 (VCC), IC10.14 (VCC), IC11.14 (VCC), IC12.20 (VCC), IC13.14 (VCC), IC14.20 (VCC), IC15.20 (VCC), IC16.20 (VCC), IC17.14 (VCC), IC18.14 (VCC), IC19.14 (VCC), IC20.14 (VCC), IC21.20 (VCC), IC22.20 (VCC), IC23.20 (VCC), IC24.20 (VCC), IC25.20 (VCC), IC36.20 (VCC), IC37.14 (VCC), IC38.1 (DIR), IC38.20 (VCC), IC39.14 (VCC), R40.2, SV_ALU_1.1, SV_ALU_1.36, SV_ALU_2.1, SV_ALU_2.36, SV_ALU_SUP1.1, SV_ALU_SUP1.3, SV_ALU_SUP1.5, SV_ALU_SUP2.1, SV_ALU_SUP2.3, SV_ALU_SUP2.5, SV_ALU_SUP3.1, SV_ALU_SUP3.3, SV_ALU_SUP3.5, SV_ALU_SUP4.1, SV_ALU_SUP4.3, SV_ALU_SUP4.5, SV_ALU_SUP5.1, SV_ALU_SUP5.3, SV_ALU_SUP5.5, SV_ALU_SUP6.1, SV_ALU_SUP6.3, SV_ALU_SUP6.5
XOR: IC3.9 (8), IC16.19 (G), R50.1

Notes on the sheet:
Right Hand

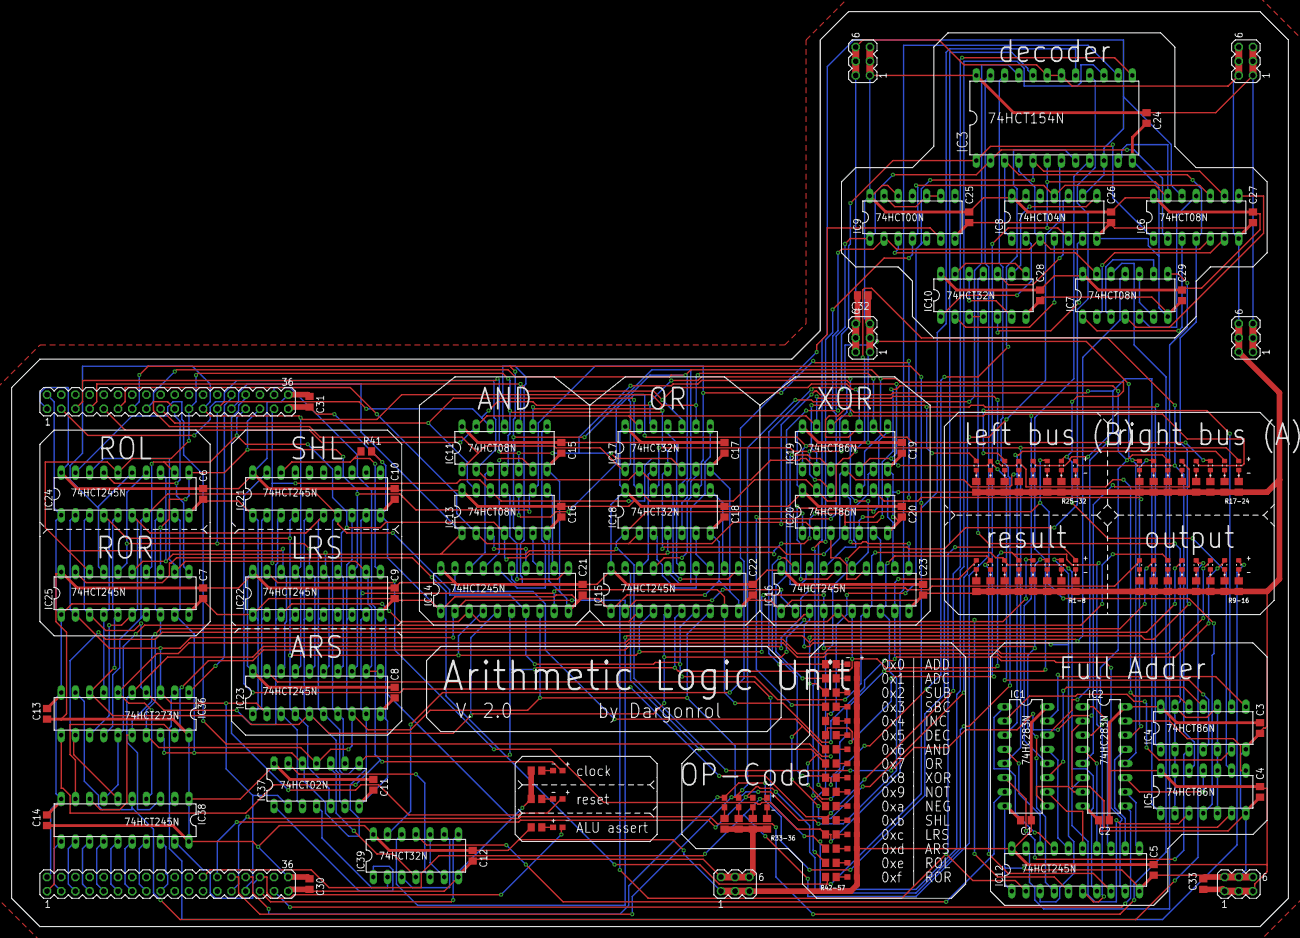
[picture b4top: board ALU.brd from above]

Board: 2 copper layers, 228.6 x 163.8 mm, 181 parts (0 on the bottom side), 193 nets.
